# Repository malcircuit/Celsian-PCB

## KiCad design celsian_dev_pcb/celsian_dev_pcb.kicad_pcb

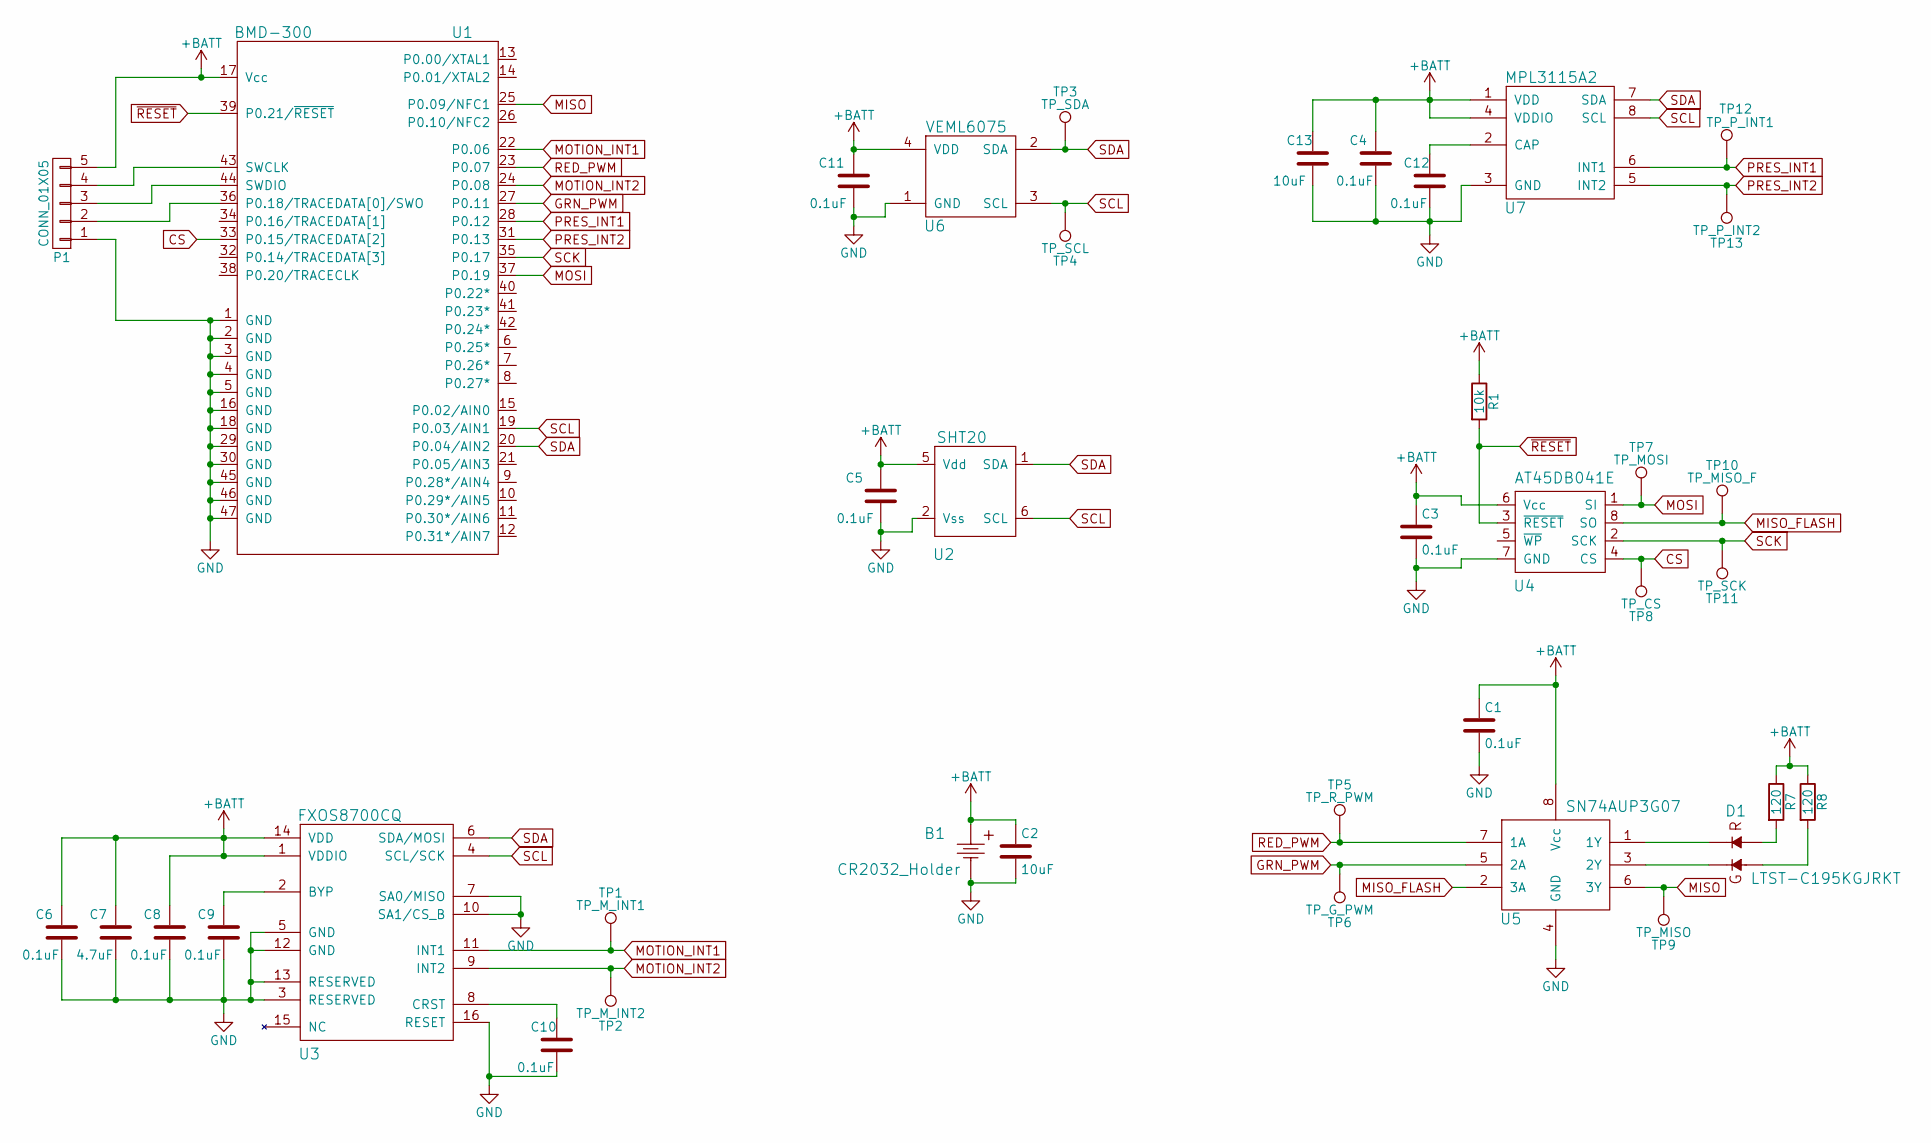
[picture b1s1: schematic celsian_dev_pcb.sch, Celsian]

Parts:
B1: CR2032_Holder; BU2032SM-HD-G
C1, C3, C4, C5, C6, C8, C9, C10, C11, C12: 0.1uF; C_0603
C2, C13: 10uF; C_0603_HandSoldering
C7: 4.7uF; C_0603
D1: LTST-C195KGJRKT
P1: CONN_01X05; Pin_Header_Straight_1x05
R1: 10k; R_0603
R7, R8: 120; R_0603
TP1: TP_M_INT1; Test_Point
TP2: TP_M_INT2; Test_Point
TP3: TP_SDA; Test_Point
TP4: TP_SCL; Test_Point
TP5: TP_R_PWM; Test_Point
TP6: TP_G_PWM; Test_Point
TP7: TP_MOSI; Test_Point
TP8: TP_CS; Test_Point
TP9: TP_MISO; Test_Point
TP10: TP_MISO_F; Test_Point
TP11: TP_SCK; Test_Point
TP12: TP_P_INT1; Test_Point
TP13: TP_P_INT2; Test_Point
U1: BMD-300
U2: SHT20
U3: FXOS8700CQ
U4: AT45DB041E; SOIC-8_3.9x4.9mm_Pitch1.27mm
U5: SN74AUP3G07
U6: VEML6075
U7: MPL3115A2

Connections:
+BATT: B1.1, C1.1, C2.1, C3.1, C4.1, C5.1, C6.1, C7.1, C8.1, C11.1, C13.1, P1.5, R1.1, R7.1, R8.1, U1.17 (Vcc), U2.5 (Vdd), U3.1 (VDDIO), U3.14 (VDD), U4.6 (Vcc), U5.8 (Vcc), U6.4 (VDD), U7.1 (VDD), U7.4 (VDDIO)
CS: TP8.1, U1.33 (P0.15/TRACEDATA[2]), U4.4 (CS)
GND: B1.2, C1.2, C2.2, C3.2, C4.2, C5.2, C6.2, C7.2, C8.2, C9.2, C10.2, C11.2, C12.2, C13.2, P1.1, U1.1 (GND), U1.2 (GND), U1.3 (GND), U1.4 (GND), U1.5 (GND), U1.16 (GND), U1.18 (GND), U1.29 (GND), U1.30 (GND), U1.45 (GND), U1.46 (GND), U1.47 (GND), U2.2 (Vss), U3.3 (RESERVED), U3.5 (GND), U3.7 (SA0/MISO), U3.10 (SA1/CS_B), U3.12 (GND), U3.13 (RESERVED), U3.16 (RESET), U4.7 (GND), U5.4 (GND), U6.1 (GND), U7.3 (GND)
GRN_PWM: TP6.1, U1.27 (P0.11), U5.5 (2A)
MISO: TP9.1, U1.25 (P0.09/NFC1), U5.6 (3Y)
MISO_FLASH: TP10.1, U4.8 (SO), U5.2 (3A)
MOSI: TP7.1, U1.37 (P0.19), U4.1 (SI)
MOTION_INT1: TP1.1, U1.22 (P0.06), U3.11 (INT1)
MOTION_INT2: TP2.1, U1.24 (P0.08), U3.9 (INT2)
unnamed: C9.1, U3.2 (BYP)
unnamed: C10.1, U3.8 (CRST)
unnamed: C12.1, U7.2 (CAP)
unnamed: D1.1 (GREEN_ANODE), R8.2
unnamed: D1.2 (RED_ANODE), R7.2
unnamed: D1.3 (GREEN_CATHODE), U5.3 (2Y)
unnamed: D1.4 (RED_CATHODE), U5.1 (1Y)
unnamed: P1.2, U1.36 (P0.18/TRACEDATA[0]/SWO)
unnamed: P1.3, U1.44 (SWDIO)
unnamed: P1.4, U1.43 (SWCLK)
PRES_INT1: TP12.1, U1.28 (P0.12), U7.6 (INT1)
PRES_INT2: TP13.1, U1.31 (P0.13), U7.5 (INT2)
RED_PWM: TP5.1, U1.23 (P0.07), U5.7 (1A)
SCK: TP11.1, U1.35 (P0.17), U4.2 (SCK)
SCL: TP4.1, U1.19 (P0.03/AIN1), U2.6 (SCL), U3.4 (SCL/SCK), U6.3 (SCL), U7.8 (SCL)
SDA: TP3.1, U1.20 (P0.04/AIN2), U2.1 (SDA), U3.6 (SDA/MOSI), U6.2 (SDA), U7.7 (SDA)
~RESET: R1.2, U1.39 (P0.21/~RESET), U4.3 (~RESET)

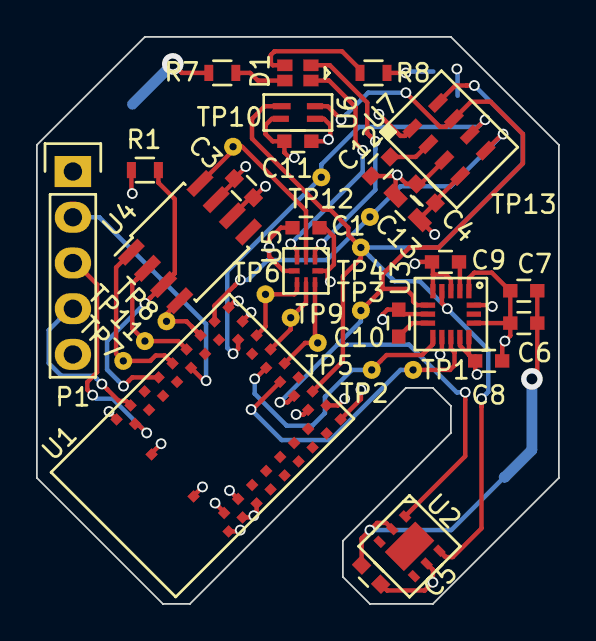
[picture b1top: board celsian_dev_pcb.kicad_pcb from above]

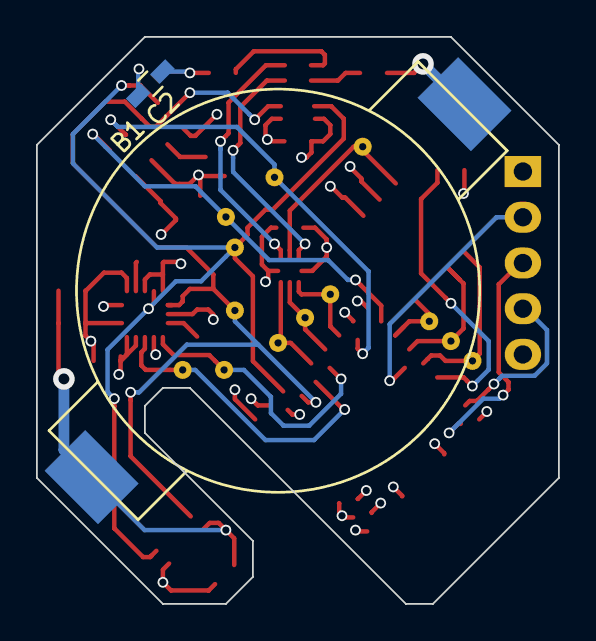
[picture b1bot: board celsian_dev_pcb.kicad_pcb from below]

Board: 4 copper layers, 29.0 x 31.5 mm, 39 parts (2 on the bottom side), 26 nets.
